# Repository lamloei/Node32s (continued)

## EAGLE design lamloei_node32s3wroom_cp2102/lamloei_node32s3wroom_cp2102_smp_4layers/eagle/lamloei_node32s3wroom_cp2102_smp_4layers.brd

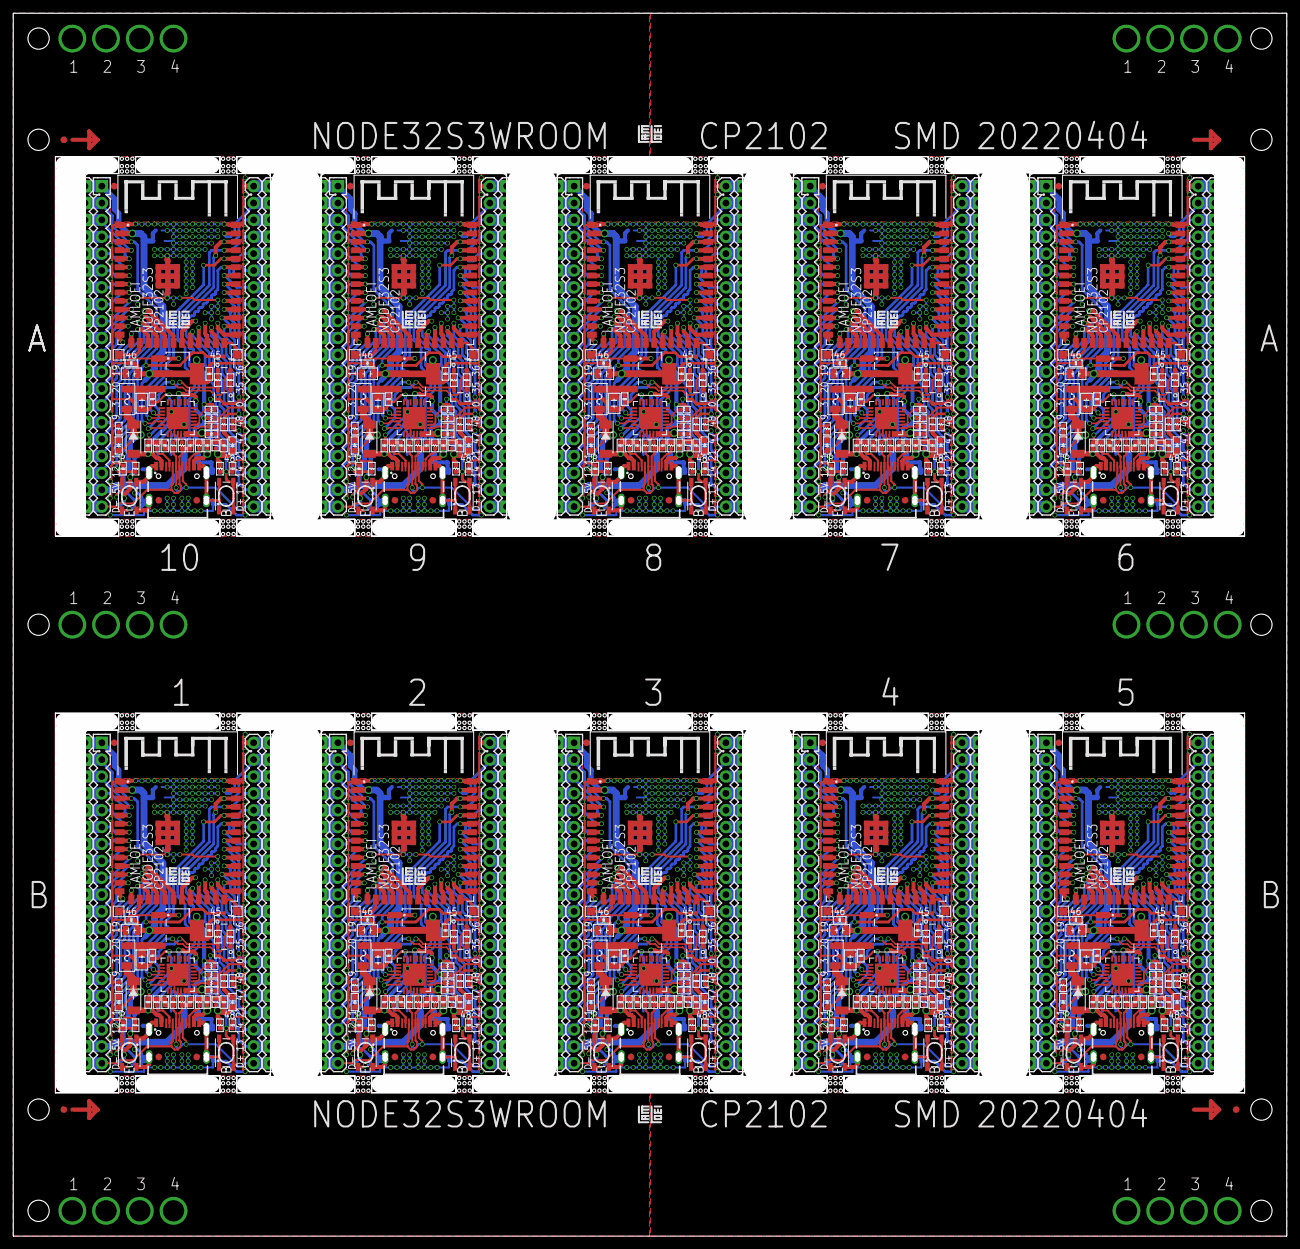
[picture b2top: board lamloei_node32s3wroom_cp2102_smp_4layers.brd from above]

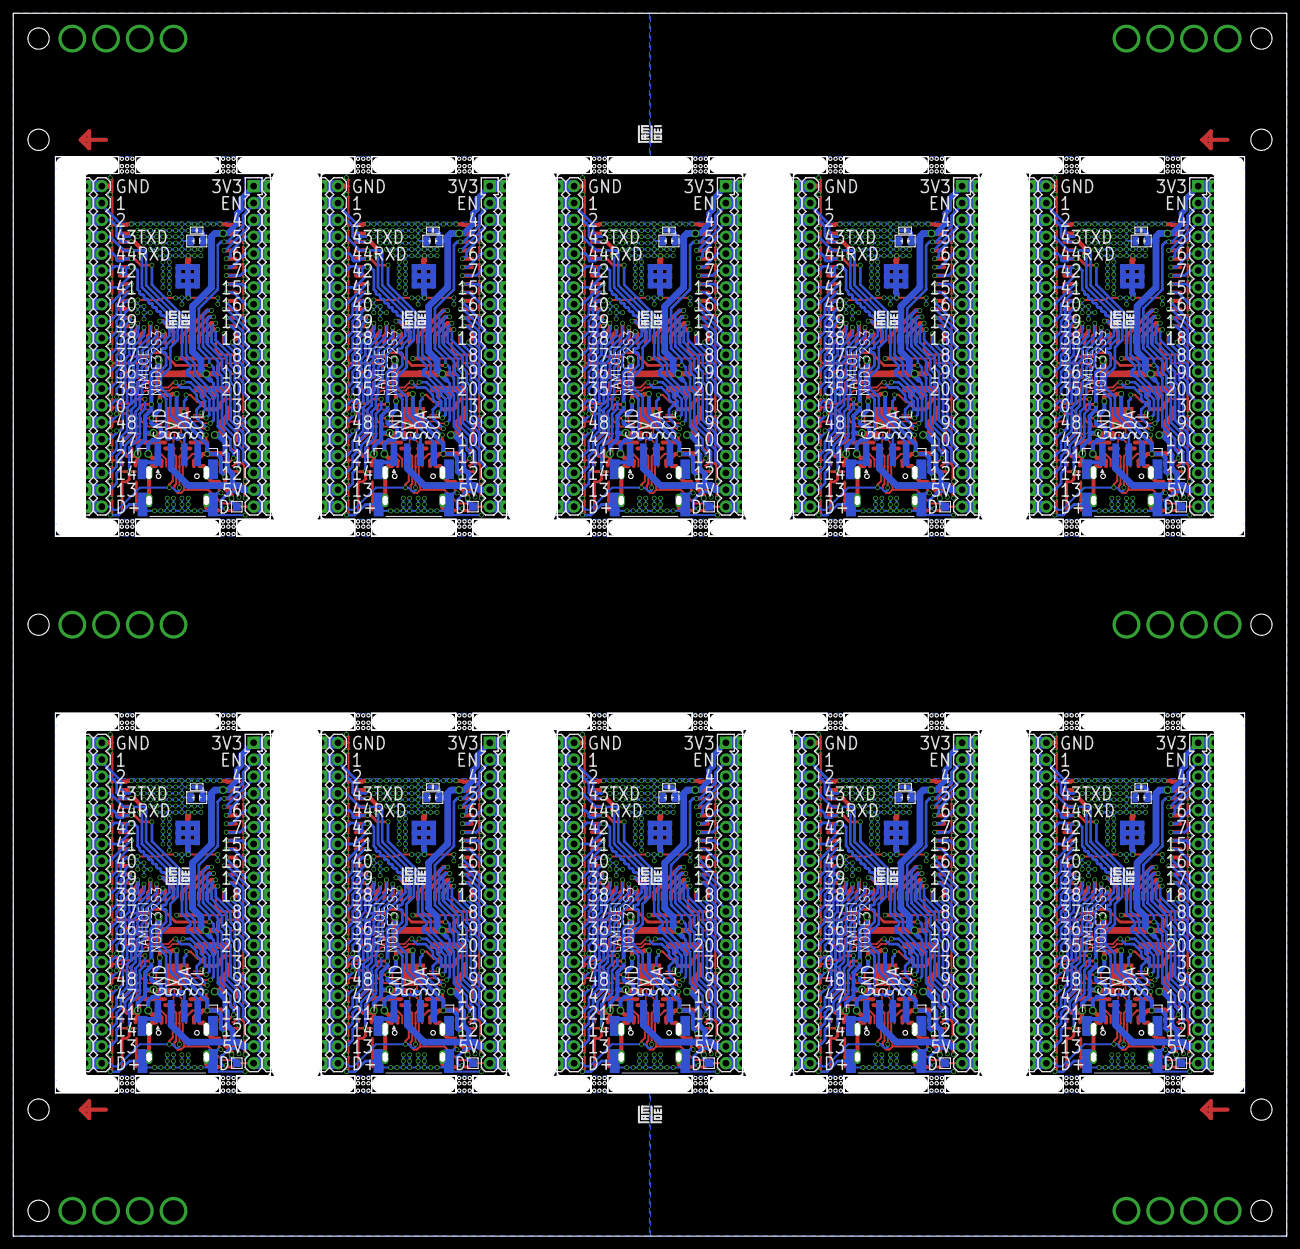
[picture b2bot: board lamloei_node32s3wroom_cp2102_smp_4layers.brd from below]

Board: 4 copper layers, 191.8 x 184.2 mm, 557 parts (52 on the bottom side), 560 nets.

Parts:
C1, C20, C33, C46, C59, C72, C85, C98, C111, C124: 1u; GRM155R70J105KA12D
C2, C3, C6, C7, C8, C10, C11, C13, C16, C17, C18, C19, C22, C24, C25, C26, C29, C30, C31, C32, C35, C37, C38, C39, C42, C43, C44, C45, C48, C50, C51, C52, C55, C56, C57, C58, C61, C63, C64, C65, C68, C69, C70, C71, C74, C76, C77, C78, C81, C82, C83, C84, C87, C89, C90, C91, C94, C95, C96, C97, C100, C102, C103, C104, C107, C108, C109, C110, C113, C115, C116, C117, C120, C121, C122, C123, C126, C128, C129, C130: 100n; GCM155R71H104KE02D
C4, C5, C14, C15, C27, C28, C40, C41, C53, C54, C66, C67, C79, C80, C92, C93, C105, C106, C118, C119: 47p; GCM1555C1H470JA16D
C9, C12, C21, C23, C34, C36, C47, C49, C60, C62, C73, C75, C86, C88, C99, C101, C112, C114, C125, C127: 22u; GCM21BR71H105KA03L
CB1, CB3, CB5, CB7, CB9, CB11, CB13, CB15, CB17, CB19: 22u; GCM21BR71H105KA03L
CB2, CB4, CB6, CB8, CB10, CB12, CB14, CB16, CB18, CB20: 100n; GCM155R71H104KE02D
D1, D2, D3, D4, D5, D6, D7, D8, D9, D10: PMEG4050EP,115
F1, F2, F3, F4, F5, F6, F7, F8, F9, F10: MF-NSMF050-2
J1, J2, J7, J8, J13, J14, J19, J20, J25, J26, J31, J32, J37, J38, J43, J44, J49, J50, J55, J56: 1 20P 2.54MM; HEADER-120
J3, J4, J9, J10, J15, J16, J21, J22, J27, J28, J33, J34, J39, J40, J45, J46, J51, J52, J57, J58: HEADER-101-SMD
J5, J6, J11, J12, J17, J18, J23, J24, J29, J30, J35, J36, J41, J42, J47, J48, J53, J54, J59, J60: HEADER-120
JB1, JB3, JB5, JB7, JB9, JB11, JB13, JB15, JB17, JB19: 1 4P 2.0MM; A2012WR-S-4P
JB2, JB4, JB6, JB8, JB10, JB12, JB14, JB16, JB18, JB20: HEADER-101-SMD
LED1, LED3, LED5, LED7, LED9, LED11, LED13, LED15, LED17, LED19: BLUE; 19-217BHC-ZL1M2RY3T
LED2, LED4, LED6, LED8, LED10, LED12, LED14, LED16, LED18, LED20: YELLOW; 19-213/Y2C-CQ2R2L/3T(CY)
Q1, Q2, Q3, Q4, Q5, Q6, Q7, Q8, Q9, Q10, Q11, Q12, Q13, Q14, Q15, Q16, Q17, Q18, Q19, Q20: BC847B,215
R1, R2, R9, R12, R13, R14, R19, R20, R21, R24, R25, R26, R33, R34, R35, R38, R39, R40, R47, R48, R49, R52, R53, R54, R61, R62, R63, R66, R67, R68, R75, R76, R77, R80, R81, R82, R89, R90, R91, R94, R95, R96, R103, R104, R105, R108, R109, R110, R117, R118, R119, R122, R123, R124, R131, R132, R133, R136, R137, R138: 12K; R0402
R3, R6, R17, R18, R31, R32, R45, R46, R59, R60, R73, R74, R87, R88, R101, R102, R115, R116, R129, R130: 5K1; R0402
R4, R5, R15, R16, R29, R30, R43, R44, R57, R58, R71, R72, R85, R86, R99, R100, R113, R114, R127, R128: 27R; R0402
R7, R8, R22, R23, R36, R37, R50, R51, R64, R65, R78, R79, R92, R93, R106, R107, R120, R121, R134, R135: 2K2; R0402
R10, R28, R42, R56, R70, R84, R98, R112, R126, R140: 47K; R0402
R11, R27, R41, R55, R69, R83, R97, R111, R125, R139: 24K; R0402
SW1, SW2, SW3, SW4, SW5, SW6, SW7, SW8, SW9, SW10, SW11, SW12, SW13, SW14, SW15, SW16, SW17, SW18, SW19, SW20: K2-1808SN-A4SW-01
TZ1, TZ2, TZ3, TZ4, TZ5, TZ6, TZ7, TZ8, TZ9, TZ10: LXES15AAA1-153
U1, U5, U8, U11, U14, U17, U20, U23, U26, U29: ESP32-S3-WROOM
U2, U6, U9, U12, U15, U18, U21, U24, U27, U30: CP2102N-A02-GQFN28R
U3, U4, U7, U10, U13, U16, U19, U22, U25, U28: LM1117MPX-3.3/NOPB
USB1, USB2, USB3, USB4, USB5, USB6, USB7, USB8, USB9, USB10: TYPE-C-31-M-12
ZFC1, ZFC2, ZFC3: FIDUCIAL1X2; FIDUCIAL-1X2
ZFD1, ZFD2, ZFD3, ZFD4, ZFD5, ZFD6, ZFD7, ZFD8, ZFD9, ZFD10, ZFD11, ZFD12, ZFD13, ZFD14, ZFD15, ZFD16, ZFD17, ZFD18, ZFD19, ZFD20, ZFD21, ZFD22, ZFD23, ZFD24, ZFD25, ZFD26, ZFD27, ZFD28, ZFD29, ZFD30: FIDUCIAL1X2; FIDUCIAL-1X2
ZL1, ZL2, ZL3, ZL4, ZL5, ZL6, ZL7, ZL8, ZL9, ZL10, ZL11, ZL12, ZL13, ZL14, ZL15, ZL16, ZL17, ZL18, ZL19, ZL20: LAMLEOI_LOGO_3
ZLC1, ZLC2, ZLC3, ZLC4: LAMLEOI_LOGO_3

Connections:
3.3V: C7.2, C8.2, C11.2, C12.2, C13.2, CB1.2, CB2.2, J1.P1, J5.P1, LED2.2, R1.2, R2.2, R12.1, TZ1.2, U1.2, U2.6, U2.7, U3.2, U3.4
3.3V1: C18.2, C23.2, C24.2, C25.2, C26.2, CB3.2, CB4.2, J7.P1, J11.P1, LED4.2, R19.2, R20.2, R26.1, TZ2.2, U4.2, U4.4, U5.2, U6.6, U6.7
3.3V2: C31.2, C36.2, C37.2, C38.2, C39.2, CB5.2, CB6.2, J13.P1, J17.P1, LED6.2, R33.2, R34.2, R40.1, TZ3.2, U7.2, U7.4, U8.2, U9.6, U9.7
3.3V3: C44.2, C49.2, C50.2, C51.2, C52.2, CB7.2, CB8.2, J19.P1, J23.P1, LED8.2, R47.2, R48.2, R54.1, TZ4.2, U10.2, U10.4, U11.2, U12.6, U12.7
3.3V4: C57.2, C62.2, C63.2, C64.2, C65.2, CB9.2, CB10.2, J25.P1, J29.P1, LED10.2, R61.2, R62.2, R68.1, TZ5.2, U13.2, U13.4, U14.2, U15.6, U15.7
3.3V5: C70.2, C75.2, C76.2, C77.2, C78.2, CB11.2, CB12.2, J31.P1, J35.P1, LED12.2, R75.2, R76.2, R82.1, TZ6.2, U16.2, U16.4, U17.2, U18.6, U18.7
3.3V6: C83.2, C88.2, C89.2, C90.2, C91.2, CB13.2, CB14.2, J37.P1, J41.P1, LED14.2, R89.2, R90.2, R96.1, TZ7.2, U19.2, U19.4, U20.2, U21.6, U21.7
3.3V7: C96.2, C101.2, C102.2, C103.2, C104.2, CB15.2, CB16.2, J43.P1, J47.P1, LED16.2, R103.2, R104.2, R110.1, TZ8.2, U22.2, U22.4, U23.2, U24.6, U24.7
3.3V8: C109.2, C114.2, C115.2, C116.2, C117.2, CB17.2, CB18.2, J49.P1, J53.P1, LED18.2, R117.2, R118.2, R124.1, TZ9.2, U25.2, U25.4, U26.2, U27.6, U27.7
3.3V9: C122.2, C127.2, C128.2, C129.2, C130.2, CB19.2, CB20.2, J55.P1, J59.P1, LED20.2, R131.2, R132.2, R138.1, TZ10.2, U28.2, U28.4, U29.2, U30.6, U30.7
5V: D1.1, F1.1, J1.P19, J5.P19, JB1.2, LED1.2
5V1: D2.1, F2.1, J7.P19, J11.P19, JB3.2, LED3.2
5V2: D3.1, F3.1, J13.P19, J17.P19, JB5.2, LED5.2
5V3: D4.1, F4.1, J19.P19, J23.P19, JB7.2, LED7.2
5V4: D5.1, F5.1, J25.P19, J29.P19, JB9.2, LED9.2
5V5: D6.1, F6.1, J31.P19, J35.P19, JB11.2, LED11.2
5V6: D7.1, F7.1, J37.P19, J41.P19, JB13.2, LED13.2
5V7: D8.1, F8.1, J43.P19, J47.P19, JB15.2, LED15.2
5V8: D9.1, F9.1, J49.P19, J53.P19, JB17.2, LED17.2
5V9: D10.1, F10.1, J55.P19, J59.P19, JB19.2, LED19.2
CC1: R3.2, USB1.A5
CC2: R6.2, USB1.B5
CC3: R17.2, USB2.A5
CC4: R18.2, USB2.B5
CC5: R31.2, USB3.A5
CC6: R32.2, USB3.B5
CC7: R45.2, USB4.A5
CC8: R46.2, USB4.B5
CC9: R59.2, USB5.A5
CC10: R60.2, USB5.B5
CC11: R73.2, USB6.A5
CC12: R74.2, USB6.B5
CC13: R87.2, USB7.A5
CC14: R88.2, USB7.B5
CC15: R101.2, USB8.A5
CC16: R102.2, USB8.B5
CC17: R115.2, USB9.A5
CC18: R116.2, USB9.B5
CC19: R129.2, USB10.A5
CC20: R130.2, USB10.B5
DM: C5.2, J1.P20, J5.P20, R5.1, USB1.A7, USB1.B7
DM1: C14.2, J7.P20, J11.P20, R16.1, USB2.A7, USB2.B7
DM2: C27.2, J13.P20, J17.P20, R30.1, USB3.A7, USB3.B7
DM3: C40.2, J19.P20, J23.P20, R44.1, USB4.A7, USB4.B7
DM4: C53.2, J25.P20, J29.P20, R58.1, USB5.A7, USB5.B7
DM5: C66.2, J31.P20, J35.P20, R72.1, USB6.A7, USB6.B7
DM6: C79.2, J37.P20, J41.P20, R86.1, USB7.A7, USB7.B7
DM7: C92.2, J43.P20, J47.P20, R100.1, USB8.A7, USB8.B7
DM8: C105.2, J49.P20, J53.P20, R114.1, USB9.A7, USB9.B7
DM9: C118.2, J55.P20, J59.P20, R128.1, USB10.A7, USB10.B7
DP: C4.2, J2.P20, J6.P20, R4.1, USB1.A6, USB1.B6
DP1: C15.2, J8.P20, J12.P20, R15.1, USB2.A6, USB2.B6
DP2: C28.2, J14.P20, J18.P20, R29.1, USB3.A6, USB3.B6
DP3: C41.2, J20.P20, J24.P20, R43.1, USB4.A6, USB4.B6
DP4: C54.2, J26.P20, J30.P20, R57.1, USB5.A6, USB5.B6
DP5: C67.2, J32.P20, J36.P20, R71.1, USB6.A6, USB6.B6
DP6: C80.2, J38.P20, J42.P20, R85.1, USB7.A6, USB7.B6
DP7: C93.2, J44.P20, J48.P20, R99.1, USB8.A6, USB8.B6
DP8: C106.2, J50.P20, J54.P20, R113.1, USB9.A6, USB9.B6
DP9: C119.2, J56.P20, J60.P20, R127.1, USB10.A6, USB10.B6
DTR: Q1.E, R13.1, U2.28
DTR1: Q4.E, R24.1, U6.28
DTR2: Q6.E, R38.1, U9.28
DTR3: Q8.E, R52.1, U12.28
DTR4: Q10.E, R66.1, U15.28
DTR5: Q12.E, R80.1, U18.28
DTR6: Q14.E, R94.1, U21.28
DTR7: Q16.E, R108.1, U24.28
DTR8: Q18.E, R122.1, U27.28
DTR9: Q20.E, R136.1, U30.28
EN: C1.2, J1.P2, J5.P2, Q2.C, R1.1, SW1.3, SW1.4, U1.3
EN1: C20.2, J7.P2, J11.P2, Q3.C, R19.1, SW3.3, SW3.4, U5.3
EN2: C33.2, J13.P2, J17.P2, Q5.C, R33.1, SW5.3, SW5.4, U8.3
EN3: C46.2, J19.P2, J23.P2, Q7.C, R47.1, SW7.3, SW7.4, U11.3
EN4: C59.2, J25.P2, J29.P2, Q9.C, R61.1, SW9.3, SW9.4, U14.3
EN5: C72.2, J31.P2, J35.P2, Q11.C, R75.1, SW11.3, SW11.4, U17.3
EN6: C85.2, J37.P2, J41.P2, Q13.C, R89.1, SW13.3, SW13.4, U20.3
EN7: C98.2, J43.P2, J47.P2, Q15.C, R103.1, SW15.3, SW15.4, U23.3
EN8: C111.2, J49.P2, J53.P2, Q17.C, R117.1, SW17.3, SW17.4, U26.3
EN9: C124.2, J55.P2, J59.P2, Q19.C, R131.1, SW19.3, SW19.4, U29.3
GND: C1.1, C2.1, C3.1, C4.1, C5.1, C6.1, C7.1, C8.1, C9.1, C10.1, C11.1, C12.1, C13.1, CB1.1, CB2.1, J2.P1, J6.P1, JB1.1, JB1.G1, JB1.G2, JB1.G3, JB1.G4, R3.1, R6.1, R7.1, R9.1, R10.1, SW1.1, SW1.2, SW2.1, SW2.2, TZ1.1, U1.1, U1.1.1, U1.1.2, U1.1.3, U1.1.4, U1.1.5, U1.1.6, U1.1.7, U1.1.8, U1.1.9, U1.1.10, U1.1.11, U1.1.12, U1.1.13, U1.1.14, U1.1.15, U1.1.16, U1.1.17, U1.1.18, U1.40, U2.3, U2.29, U3.1, USB1.A1B12, USB1.B1A12, USB1.S1, USB1.S2, USB1.S3, USB1.S4
GND1: C14.1, C15.1, C16.1, C17.1, C18.1, C19.1, C20.1, C21.1, C22.1, C23.1, C24.1, C25.1, C26.1, CB3.1, CB4.1, J8.P1, J12.P1, JB3.1, JB3.G1, JB3.G2, JB3.G3, JB3.G4, R17.1, R18.1, R21.1, R22.1, R28.1, SW3.1, SW3.2, SW4.1, SW4.2, TZ2.1, U4.1, U5.1, U5.1.1, U5.1.2, U5.1.3, U5.1.4, U5.1.5, U5.1.6, U5.1.7, U5.1.8, U5.1.9, U5.1.10, U5.1.11, U5.1.12, U5.1.13, U5.1.14, U5.1.15, U5.1.16, U5.1.17, U5.1.18, U5.40, U6.3, U6.29, USB2.A1B12, USB2.B1A12, USB2.S1, USB2.S2, USB2.S3, USB2.S4
GND2: C27.1, C28.1, C29.1, C30.1, C31.1, C32.1, C33.1, C34.1, C35.1, C36.1, C37.1, C38.1, C39.1, CB5.1, CB6.1, J14.P1, J18.P1, JB5.1, JB5.G1, JB5.G2, JB5.G3, JB5.G4, R31.1, R32.1, R35.1, R36.1, R42.1, SW5.1, SW5.2, SW6.1, SW6.2, TZ3.1, U7.1, U8.1, U8.1.1, U8.1.2, U8.1.3, U8.1.4, U8.1.5, U8.1.6, U8.1.7, U8.1.8, U8.1.9, U8.1.10, U8.1.11, U8.1.12, U8.1.13, U8.1.14, U8.1.15, U8.1.16, U8.1.17, U8.1.18, U8.40, U9.3, U9.29, USB3.A1B12, USB3.B1A12, USB3.S1, USB3.S2, USB3.S3, USB3.S4
GND3: C40.1, C41.1, C42.1, C43.1, C44.1, C45.1, C46.1, C47.1, C48.1, C49.1, C50.1, C51.1, C52.1, CB7.1, CB8.1, J20.P1, J24.P1, JB7.1, JB7.G1, JB7.G2, JB7.G3, JB7.G4, R45.1, R46.1, R49.1, R50.1, R56.1, SW7.1, SW7.2, SW8.1, SW8.2, TZ4.1, U10.1, U11.1, U11.1.1, U11.1.2, U11.1.3, U11.1.4, U11.1.5, U11.1.6, U11.1.7, U11.1.8, U11.1.9, U11.1.10, U11.1.11, U11.1.12, U11.1.13, U11.1.14, U11.1.15, U11.1.16, U11.1.17, U11.1.18, U11.40, U12.3, U12.29, USB4.A1B12, USB4.B1A12, USB4.S1, USB4.S2, USB4.S3, USB4.S4
GND4: C53.1, C54.1, C55.1, C56.1, C57.1, C58.1, C59.1, C60.1, C61.1, C62.1, C63.1, C64.1, C65.1, CB9.1, CB10.1, J26.P1, J30.P1, JB9.1, JB9.G1, JB9.G2, JB9.G3, JB9.G4, R59.1, R60.1, R63.1, R64.1, R70.1, SW9.1, SW9.2, SW10.1, SW10.2, TZ5.1, U13.1, U14.1, U14.1.1, U14.1.2, U14.1.3, U14.1.4, U14.1.5, U14.1.6, U14.1.7, U14.1.8, U14.1.9, U14.1.10, U14.1.11, U14.1.12, U14.1.13, U14.1.14, U14.1.15, U14.1.16, U14.1.17, U14.1.18, U14.40, U15.3, U15.29, USB5.A1B12, USB5.B1A12, USB5.S1, USB5.S2, USB5.S3, USB5.S4
GND5: C66.1, C67.1, C68.1, C69.1, C70.1, C71.1, C72.1, C73.1, C74.1, C75.1, C76.1, C77.1, C78.1, CB11.1, CB12.1, J32.P1, J36.P1, JB11.1, JB11.G1, JB11.G2, JB11.G3, JB11.G4, R73.1, R74.1, R77.1, R78.1, R84.1, SW11.1, SW11.2, SW12.1, SW12.2, TZ6.1, U16.1, U17.1, U17.1.1, U17.1.2, U17.1.3, U17.1.4, U17.1.5, U17.1.6, U17.1.7, U17.1.8, U17.1.9, U17.1.10, U17.1.11, U17.1.12, U17.1.13, U17.1.14, U17.1.15, U17.1.16, U17.1.17, U17.1.18, U17.40, U18.3, U18.29, USB6.A1B12, USB6.B1A12, USB6.S1, USB6.S2, USB6.S3, USB6.S4
GND6: C79.1, C80.1, C81.1, C82.1, C83.1, C84.1, C85.1, C86.1, C87.1, C88.1, C89.1, C90.1, C91.1, CB13.1, CB14.1, J38.P1, J42.P1, JB13.1, JB13.G1, JB13.G2, JB13.G3, JB13.G4, R87.1, R88.1, R91.1, R92.1, R98.1, SW13.1, SW13.2, SW14.1, SW14.2, TZ7.1, U19.1, U20.1, U20.1.1, U20.1.2, U20.1.3, U20.1.4, U20.1.5, U20.1.6, U20.1.7, U20.1.8, U20.1.9, U20.1.10, U20.1.11, U20.1.12, U20.1.13, U20.1.14, U20.1.15, U20.1.16, U20.1.17, U20.1.18, U20.40, U21.3, U21.29, USB7.A1B12, USB7.B1A12, USB7.S1, USB7.S2, USB7.S3, USB7.S4
GND7: C92.1, C93.1, C94.1, C95.1, C96.1, C97.1, C98.1, C99.1, C100.1, C101.1, C102.1, C103.1, C104.1, CB15.1, CB16.1, J44.P1, J48.P1, JB15.1, JB15.G1, JB15.G2, JB15.G3, JB15.G4, R101.1, R102.1, R105.1, R106.1, R112.1, SW15.1, SW15.2, SW16.1, SW16.2, TZ8.1, U22.1, U23.1, U23.1.1, U23.1.2, U23.1.3, U23.1.4, U23.1.5, U23.1.6, U23.1.7, U23.1.8, U23.1.9, U23.1.10, U23.1.11, U23.1.12, U23.1.13, U23.1.14, U23.1.15, U23.1.16, U23.1.17, U23.1.18, U23.40, U24.3, U24.29, USB8.A1B12, USB8.B1A12, USB8.S1, USB8.S2, USB8.S3, USB8.S4
GND8: C105.1, C106.1, C107.1, C108.1, C109.1, C110.1, C111.1, C112.1, C113.1, C114.1, C115.1, C116.1, C117.1, CB17.1, CB18.1, J50.P1, J54.P1, JB17.1, JB17.G1, JB17.G2, JB17.G3, JB17.G4, R115.1, R116.1, R119.1, R120.1, R126.1, SW17.1, SW17.2, SW18.1, SW18.2, TZ9.1, U25.1, U26.1, U26.1.1, U26.1.2, U26.1.3, U26.1.4, U26.1.5, U26.1.6, U26.1.7, U26.1.8, U26.1.9, U26.1.10, U26.1.11, U26.1.12, U26.1.13, U26.1.14, U26.1.15, U26.1.16, U26.1.17, U26.1.18, U26.40, U27.3, U27.29, USB9.A1B12, USB9.B1A12, USB9.S1, USB9.S2, USB9.S3, USB9.S4
GND9: C118.1, C119.1, C120.1, C121.1, C122.1, C123.1, C124.1, C125.1, C126.1, C127.1, C128.1, C129.1, C130.1, CB19.1, CB20.1, J56.P1, J60.P1, JB19.1, JB19.G1, JB19.G2, JB19.G3, JB19.G4, R129.1, R130.1, R133.1, R134.1, R140.1, SW19.1, SW19.2, SW20.1, SW20.2, TZ10.1, U28.1, U29.1, U29.1.1, U29.1.2, U29.1.3, U29.1.4, U29.1.5, U29.1.6, U29.1.7, U29.1.8, U29.1.9, U29.1.10, U29.1.11, U29.1.12, U29.1.13, U29.1.14, U29.1.15, U29.1.16, U29.1.17, U29.1.18, U29.40, U30.3, U30.29, USB10.A1B12, USB10.B1A12, USB10.S1, USB10.S2, USB10.S3, USB10.S4
IO0: C2.2, J2.P14, J6.P14, Q1.C, R2.1, SW2.3, SW2.4, U1.27
IO1: J2.P2, J6.P2, U1.39
IO2: J2.P3, J6.P3, JB1.4, U1.38
IO3: J1.P14, J5.P14, U1.15
IO4: J1.P3, J5.P3, U1.4
IO5: J1.P4, J5.P4, U1.5
IO6: J1.P5, J5.P5, U1.6
IO7: J1.P6, J5.P6, U1.7
IO8: J1.P11, J5.P11, U1.12
IO9: J1.P15, J5.P15, U1.17
IO10: J1.P16, J5.P16, U1.18
IO11: J1.P17, J5.P17, U1.19
IO12: J1.P18, J5.P18, U1.20
IO13: J2.P19, J6.P19, U1.21
IO14: J2.P18, J6.P18, U1.22
IO15: J1.P7, J5.P7, U1.8
IO16: J1.P8, J5.P8, U1.9
IO17: J1.P9, J5.P9, U1.10
IO18: J1.P10, J5.P10, U1.11
IO19: J1.P12, J5.P12, U1.13
IO20: J1.P13, J5.P13, U1.14
IO21: J2.P17, J6.P17, U1.23
IO22: J7.P17, J11.P17, U5.19
IO23: J7.P5, J11.P5, U5.6
IO24: J7.P6, J11.P6, U5.7
IO25: J7.P11, J11.P11, U5.12
IO26: J7.P15, J11.P15, U5.17
IO27: J7.P16, J11.P16, U5.18
IO28: C19.2, J8.P14, J12.P14, Q4.C, R20.1, SW4.3, SW4.4, U5.27
IO29: J7.P3, J11.P3, U5.4
IO30: J7.P4, J11.P4, U5.5
IO31: J7.P7, J11.P7, U5.8
IO32: J7.P8, J11.P8, U5.9
IO33: J7.P9, J11.P9, U5.10
IO34: J7.P10, J11.P10, U5.11
IO35: J2.P13, J6.P13, U1.28
IO36: J2.P12, J6.P12, U1.29
IO37: J2.P11, J6.P11, U1.30
IO38: J2.P10, J6.P10, U1.31
IO39: J2.P9, J6.P9, U1.32
IO40: J2.P8, J6.P8, U1.33
IO41: J2.P7, J6.P7, U1.34
IO42: J2.P6, J6.P6, JB1.3, U1.35
IO43: J7.P12, J11.P12, U5.13
IO44: J8.P17, J12.P17, U5.23
IO45: J4.P$1, U1.26
IO46: J3.P$1, U1.16
IO47: J2.P16, J6.P16, R9.2, U1.24
IO48: J2.P15, J6.P15, R8.1, U1.25
IO49: J7.P13, J11.P13, U5.14
IO50: J7.P14, J11.P14, U5.15
IO51: J7.P18, J11.P18, U5.20
IO52: J8.P19, J12.P19, U5.21
IO53: J8.P18, J12.P18, U5.22
IO54: J8.P16, J12.P16, R21.2, U5.24
IO55: J8.P15, J12.P15, R23.1, U5.25
IO56: J8.P6, J12.P6, JB3.3, U5.35
IO57: J8.P13, J12.P13, U5.28
IO58: J8.P12, J12.P12, U5.29
IO59: J8.P11, J12.P11, U5.30
IO60: J8.P10, J12.P10, U5.31
IO61: J8.P9, J12.P9, U5.32
IO62: J8.P8, J12.P8, U5.33
IO63: J8.P7, J12.P7, U5.34
IO64: J8.P3, J12.P3, JB3.4, U5.38
IO65: J8.P2, J12.P2, U5.39
IO66: J10.P$1, U5.26
IO67: J9.P$1, U5.16
IO68: J13.P17, J17.P17, U8.19
IO69: J13.P5, J17.P5, U8.6
IO70: J13.P6, J17.P6, U8.7
IO71: J13.P11, J17.P11, U8.12
IO72: J13.P15, J17.P15, U8.17
IO73: J13.P16, J17.P16, U8.18
IO74: C32.2, J14.P14, J18.P14, Q6.C, R34.1, SW6.3, SW6.4, U8.27
IO75: J13.P3, J17.P3, U8.4
IO76: J13.P4, J17.P4, U8.5
IO77: J13.P7, J17.P7, U8.8
IO78: J13.P8, J17.P8, U8.9
IO79: J13.P9, J17.P9, U8.10
IO80: J13.P10, J17.P10, U8.11
IO81: J13.P12, J17.P12, U8.13
IO82: J14.P17, J18.P17, U8.23
IO83: J13.P13, J17.P13, U8.14
IO84: J13.P14, J17.P14, U8.15
IO85: J13.P18, J17.P18, U8.20
IO86: J14.P19, J18.P19, U8.21
IO87: J14.P18, J18.P18, U8.22
IO88: J14.P16, J18.P16, R35.2, U8.24
IO89: J14.P15, J18.P15, R37.1, U8.25
IO90: J14.P6, J18.P6, JB5.3, U8.35
IO91: J14.P13, J18.P13, U8.28
IO92: J14.P12, J18.P12, U8.29
IO93: J14.P11, J18.P11, U8.30
IO94: J14.P10, J18.P10, U8.31
IO95: J14.P9, J18.P9, U8.32
IO96: J14.P8, J18.P8, U8.33
IO97: J14.P7, J18.P7, U8.34
IO98: J14.P3, J18.P3, JB5.4, U8.38
IO99: J14.P2, J18.P2, U8.39
IO100: J16.P$1, U8.26
IO101: J15.P$1, U8.16
IO102: J19.P17, J23.P17, U11.19
IO103: J19.P5, J23.P5, U11.6
IO104: J19.P6, J23.P6, U11.7
IO105: J19.P11, J23.P11, U11.12
IO106: J19.P15, J23.P15, U11.17
IO107: J19.P16, J23.P16, U11.18
IO108: C45.2, J20.P14, J24.P14, Q8.C, R48.1, SW8.3, SW8.4, U11.27
IO109: J19.P3, J23.P3, U11.4
IO110: J19.P4, J23.P4, U11.5
IO111: J19.P7, J23.P7, U11.8
IO112: J19.P8, J23.P8, U11.9
IO113: J19.P9, J23.P9, U11.10
IO114: J19.P10, J23.P10, U11.11
IO115: J19.P12, J23.P12, U11.13
IO116: J20.P17, J24.P17, U11.23
IO117: J19.P13, J23.P13, U11.14
IO118: J19.P14, J23.P14, U11.15
IO119: J19.P18, J23.P18, U11.20
IO120: J20.P19, J24.P19, U11.21
IO121: J20.P18, J24.P18, U11.22
IO122: J20.P16, J24.P16, R49.2, U11.24
IO123: J20.P15, J24.P15, R51.1, U11.25
IO124: J20.P6, J24.P6, JB7.3, U11.35
IO125: J20.P13, J24.P13, U11.28
IO126: J20.P12, J24.P12, U11.29
IO127: J20.P11, J24.P11, U11.30
IO128: J20.P10, J24.P10, U11.31
IO129: J20.P9, J24.P9, U11.32
IO130: J20.P8, J24.P8, U11.33
IO131: J20.P7, J24.P7, U11.34
IO132: J20.P3, J24.P3, JB7.4, U11.38
IO133: J20.P2, J24.P2, U11.39
IO134: J22.P$1, U11.26
IO135: J21.P$1, U11.16
IO136: J25.P17, J29.P17, U14.19
IO137: J25.P5, J29.P5, U14.6
IO138: J25.P6, J29.P6, U14.7
IO139: J25.P11, J29.P11, U14.12
IO140: J25.P15, J29.P15, U14.17
IO141: J25.P16, J29.P16, U14.18
IO142: C58.2, J26.P14, J30.P14, Q10.C, R62.1, SW10.3, SW10.4, U14.27
IO143: J25.P3, J29.P3, U14.4
IO144: J25.P4, J29.P4, U14.5
IO145: J25.P7, J29.P7, U14.8
IO146: J25.P8, J29.P8, U14.9
IO147: J25.P9, J29.P9, U14.10
IO148: J25.P10, J29.P10, U14.11
IO149: J25.P12, J29.P12, U14.13
IO150: J26.P17, J30.P17, U14.23
IO151: J25.P13, J29.P13, U14.14
IO152: J25.P14, J29.P14, U14.15
IO153: J25.P18, J29.P18, U14.20
IO154: J26.P19, J30.P19, U14.21
IO155: J26.P18, J30.P18, U14.22
IO156: J26.P16, J30.P16, R63.2, U14.24
IO157: J26.P15, J30.P15, R65.1, U14.25
IO158: J26.P6, J30.P6, JB9.3, U14.35
IO159: J26.P13, J30.P13, U14.28
IO160: J26.P12, J30.P12, U14.29
IO161: J26.P11, J30.P11, U14.30
IO162: J26.P10, J30.P10, U14.31
IO163: J26.P9, J30.P9, U14.32
IO164: J26.P8, J30.P8, U14.33
IO165: J26.P7, J30.P7, U14.34
IO166: J26.P3, J30.P3, JB9.4, U14.38
IO167: J26.P2, J30.P2, U14.39
IO168: J28.P$1, U14.26
IO169: J27.P$1, U14.16
IO170: J31.P17, J35.P17, U17.19
IO171: J31.P5, J35.P5, U17.6
IO172: J31.P6, J35.P6, U17.7
IO173: J31.P11, J35.P11, U17.12
IO174: J31.P15, J35.P15, U17.17
IO175: J31.P16, J35.P16, U17.18
IO176: C71.2, J32.P14, J36.P14, Q12.C, R76.1, SW12.3, SW12.4, U17.27
IO177: J31.P3, J35.P3, U17.4
IO178: J31.P4, J35.P4, U17.5
IO179: J31.P7, J35.P7, U17.8
IO180: J31.P8, J35.P8, U17.9
IO181: J31.P9, J35.P9, U17.10
IO182: J31.P10, J35.P10, U17.11
IO183: J31.P12, J35.P12, U17.13
IO184: J32.P17, J36.P17, U17.23
IO185: J31.P13, J35.P13, U17.14
IO186: J31.P14, J35.P14, U17.15
IO187: J31.P18, J35.P18, U17.20
IO188: J32.P19, J36.P19, U17.21
IO189: J32.P18, J36.P18, U17.22
IO190: J32.P16, J36.P16, R77.2, U17.24
IO191: J32.P15, J36.P15, R79.1, U17.25
IO192: J32.P6, J36.P6, JB11.3, U17.35
IO193: J32.P13, J36.P13, U17.28
IO194: J32.P12, J36.P12, U17.29
IO195: J32.P11, J36.P11, U17.30
IO196: J32.P10, J36.P10, U17.31
IO197: J32.P9, J36.P9, U17.32
IO198: J32.P8, J36.P8, U17.33
IO199: J32.P7, J36.P7, U17.34
IO200: J32.P3, J36.P3, JB11.4, U17.38
IO201: J32.P2, J36.P2, U17.39
IO202: J34.P$1, U17.26
IO203: J33.P$1, U17.16
IO204: J37.P17, J41.P17, U20.19
IO205: J37.P5, J41.P5, U20.6
IO206: J37.P6, J41.P6, U20.7
IO207: J37.P11, J41.P11, U20.12
IO208: J37.P15, J41.P15, U20.17
IO209: J37.P16, J41.P16, U20.18
IO210: C84.2, J38.P14, J42.P14, Q14.C, R90.1, SW14.3, SW14.4, U20.27
IO211: J37.P3, J41.P3, U20.4
IO212: J37.P4, J41.P4, U20.5
IO213: J37.P7, J41.P7, U20.8
IO214: J37.P8, J41.P8, U20.9
IO215: J37.P9, J41.P9, U20.10
IO216: J37.P10, J41.P10, U20.11
IO217: J37.P12, J41.P12, U20.13
IO218: J38.P17, J42.P17, U20.23
IO219: J37.P13, J41.P13, U20.14
IO220: J37.P14, J41.P14, U20.15
IO221: J37.P18, J41.P18, U20.20
IO222: J38.P19, J42.P19, U20.21
IO223: J38.P18, J42.P18, U20.22
IO224: J38.P16, J42.P16, R91.2, U20.24
IO225: J38.P15, J42.P15, R93.1, U20.25
IO226: J38.P6, J42.P6, JB13.3, U20.35
IO227: J38.P13, J42.P13, U20.28
IO228: J38.P12, J42.P12, U20.29
IO229: J38.P11, J42.P11, U20.30
IO230: J38.P10, J42.P10, U20.31
IO231: J38.P9, J42.P9, U20.32
IO232: J38.P8, J42.P8, U20.33
IO233: J38.P7, J42.P7, U20.34
IO234: J38.P3, J42.P3, JB13.4, U20.38
IO235: J38.P2, J42.P2, U20.39
IO236: J40.P$1, U20.26
IO237: J39.P$1, U20.16
IO238: J43.P17, J47.P17, U23.19
IO239: J43.P5, J47.P5, U23.6
IO240: J43.P6, J47.P6, U23.7
IO241: J43.P11, J47.P11, U23.12
IO242: J43.P15, J47.P15, U23.17
IO243: J43.P16, J47.P16, U23.18
IO244: C97.2, J44.P14, J48.P14, Q16.C, R104.1, SW16.3, SW16.4, U23.27
IO245: J43.P3, J47.P3, U23.4
IO246: J43.P4, J47.P4, U23.5
IO247: J43.P7, J47.P7, U23.8
IO248: J43.P8, J47.P8, U23.9
IO249: J43.P9, J47.P9, U23.10
IO250: J43.P10, J47.P10, U23.11
IO251: J43.P12, J47.P12, U23.13
IO252: J44.P17, J48.P17, U23.23
IO253: J43.P13, J47.P13, U23.14
IO254: J43.P14, J47.P14, U23.15
IO255: J43.P18, J47.P18, U23.20
IO256: J44.P19, J48.P19, U23.21
IO257: J44.P18, J48.P18, U23.22
IO258: J44.P16, J48.P16, R105.2, U23.24
IO259: J44.P15, J48.P15, R107.1, U23.25
IO260: J44.P6, J48.P6, JB15.3, U23.35
IO261: J44.P13, J48.P13, U23.28
IO262: J44.P12, J48.P12, U23.29
IO263: J44.P11, J48.P11, U23.30
IO264: J44.P10, J48.P10, U23.31
IO265: J44.P9, J48.P9, U23.32
IO266: J44.P8, J48.P8, U23.33
IO267: J44.P7, J48.P7, U23.34
IO268: J44.P3, J48.P3, JB15.4, U23.38
IO269: J44.P2, J48.P2, U23.39
IO270: J46.P$1, U23.26
IO271: J45.P$1, U23.16
IO272: J49.P17, J53.P17, U26.19
IO273: J49.P5, J53.P5, U26.6
IO274: J49.P6, J53.P6, U26.7
IO275: J49.P11, J53.P11, U26.12
IO276: J49.P15, J53.P15, U26.17
IO277: J49.P16, J53.P16, U26.18
IO278: C110.2, J50.P14, J54.P14, Q18.C, R118.1, SW18.3, SW18.4, U26.27
IO279: J49.P3, J53.P3, U26.4
IO280: J49.P4, J53.P4, U26.5
IO281: J49.P7, J53.P7, U26.8
IO282: J49.P8, J53.P8, U26.9
IO283: J49.P9, J53.P9, U26.10
IO284: J49.P10, J53.P10, U26.11
IO285: J49.P12, J53.P12, U26.13
IO286: J50.P17, J54.P17, U26.23
IO287: J49.P13, J53.P13, U26.14
IO288: J49.P14, J53.P14, U26.15
IO289: J49.P18, J53.P18, U26.20
IO290: J50.P19, J54.P19, U26.21
IO291: J50.P18, J54.P18, U26.22
IO292: J50.P16, J54.P16, R119.2, U26.24
IO293: J50.P15, J54.P15, R121.1, U26.25
IO294: J50.P6, J54.P6, JB17.3, U26.35
IO295: J50.P13, J54.P13, U26.28
IO296: J50.P12, J54.P12, U26.29
IO297: J50.P11, J54.P11, U26.30
IO298: J50.P10, J54.P10, U26.31
IO299: J50.P9, J54.P9, U26.32
IO300: J50.P8, J54.P8, U26.33
IO301: J50.P7, J54.P7, U26.34
IO302: J50.P3, J54.P3, JB17.4, U26.38
IO303: J50.P2, J54.P2, U26.39
IO304: J52.P$1, U26.26
IO305: J51.P$1, U26.16
IO306: J55.P17, J59.P17, U29.19
IO307: J55.P5, J59.P5, U29.6
IO308: J55.P6, J59.P6, U29.7
IO309: J55.P11, J59.P11, U29.12
IO310: J55.P15, J59.P15, U29.17
IO311: J55.P16, J59.P16, U29.18
IO312: C123.2, J56.P14, J60.P14, Q20.C, R132.1, SW20.3, SW20.4, U29.27
IO313: J55.P3, J59.P3, U29.4
IO314: J55.P4, J59.P4, U29.5
IO315: J55.P7, J59.P7, U29.8
IO316: J55.P8, J59.P8, U29.9
IO317: J55.P9, J59.P9, U29.10
IO318: J55.P10, J59.P10, U29.11
IO319: J55.P12, J59.P12, U29.13
IO320: J56.P17, J60.P17, U29.23
IO321: J55.P13, J59.P13, U29.14
IO322: J55.P14, J59.P14, U29.15
IO323: J55.P18, J59.P18, U29.20
IO324: J56.P19, J60.P19, U29.21
IO325: J56.P18, J60.P18, U29.22
IO326: J56.P16, J60.P16, R133.2, U29.24
IO327: J56.P15, J60.P15, R135.1, U29.25
IO328: J56.P6, J60.P6, JB19.3, U29.35
IO329: J56.P13, J60.P13, U29.28
IO330: J56.P12, J60.P12, U29.29
IO331: J56.P11, J60.P11, U29.30
IO332: J56.P10, J60.P10, U29.31
IO333: J56.P9, J60.P9, U29.32
IO334: J56.P8, J60.P8, U29.33
IO335: J56.P7, J60.P7, U29.34
IO336: J56.P3, J60.P3, JB19.4, U29.38
IO337: J56.P2, J60.P2, U29.39
IO338: J58.P$1, U29.26
IO339: J57.P$1, U29.16
unnamed: C9.2, C10.2, F1.2, U3.3
unnamed: LED1.1, R7.2
unnamed: LED2.1, R8.2
unnamed: Q2.B, R13.2
unnamed: Q1.B, R14.2
unnamed: R5.2, U2.5
unnamed: R4.2, U2.4
unnamed: R12.2, U2.9
unnamed: R10.2, R11.2, U2.8
unnamed: C21.2, C22.2, F2.2, U4.3
unnamed: LED3.1, R22.2
unnamed: LED4.1, R23.2
unnamed: Q3.B, R24.2
unnamed: Q4.B, R25.2
unnamed: R16.2, U6.5
unnamed: R15.2, U6.4
unnamed: R26.2, U6.9
unnamed: R27.2, R28.2, U6.8
unnamed: C34.2, C35.2, F3.2, U7.3
unnamed: LED5.1, R36.2
unnamed: LED6.1, R37.2
unnamed: Q5.B, R38.2
unnamed: Q6.B, R39.2
unnamed: R30.2, U9.5
unnamed: R29.2, U9.4
unnamed: R40.2, U9.9
unnamed: R41.2, R42.2, U9.8
unnamed: C47.2, C48.2, F4.2, U10.3
unnamed: LED7.1, R50.2
unnamed: LED8.1, R51.2
unnamed: Q7.B, R52.2
unnamed: Q8.B, R53.2
unnamed: R44.2, U12.5
unnamed: R43.2, U12.4
unnamed: R54.2, U12.9
unnamed: R55.2, R56.2, U12.8
unnamed: C60.2, C61.2, F5.2, U13.3
unnamed: LED9.1, R64.2
unnamed: LED10.1, R65.2
unnamed: Q9.B, R66.2
unnamed: Q10.B, R67.2
unnamed: R58.2, U15.5
unnamed: R57.2, U15.4
unnamed: R68.2, U15.9
unnamed: R69.2, R70.2, U15.8
unnamed: C73.2, C74.2, F6.2, U16.3
unnamed: LED11.1, R78.2
unnamed: LED12.1, R79.2
unnamed: Q11.B, R80.2
unnamed: Q12.B, R81.2
unnamed: R72.2, U18.5
unnamed: R71.2, U18.4
unnamed: R82.2, U18.9
unnamed: R83.2, R84.2, U18.8
unnamed: C86.2, C87.2, F7.2, U19.3
unnamed: LED13.1, R92.2
unnamed: LED14.1, R93.2
unnamed: Q13.B, R94.2
unnamed: Q14.B, R95.2
unnamed: R86.2, U21.5
unnamed: R85.2, U21.4
unnamed: R96.2, U21.9
unnamed: R97.2, R98.2, U21.8
unnamed: C99.2, C100.2, F8.2, U22.3
unnamed: LED15.1, R106.2
unnamed: LED16.1, R107.2
unnamed: Q15.B, R108.2
unnamed: Q16.B, R109.2
unnamed: R100.2, U24.5
unnamed: R99.2, U24.4
unnamed: R110.2, U24.9
unnamed: R111.2, R112.2, U24.8
unnamed: C112.2, C113.2, F9.2, U25.3
unnamed: LED17.1, R120.2
unnamed: LED18.1, R121.2
unnamed: Q17.B, R122.2
unnamed: Q18.B, R123.2
unnamed: R114.2, U27.5
unnamed: R113.2, U27.4
unnamed: R124.2, U27.9
unnamed: R125.2, R126.2, U27.8
unnamed: C125.2, C126.2, F10.2, U28.3
unnamed: LED19.1, R134.2
unnamed: LED20.1, R135.2
unnamed: Q19.B, R136.2
unnamed: Q20.B, R137.2
unnamed: R128.2, U30.5
unnamed: R127.2, U30.4
unnamed: R138.2, U30.9
unnamed: R139.2, R140.2, U30.8
RTS: Q2.E, R14.1, U2.24
RTS1: Q3.E, R25.1, U6.24
RTS2: Q5.E, R39.1, U9.24
RTS3: Q7.E, R53.1, U12.24
RTS4: Q9.E, R67.1, U15.24
RTS5: Q11.E, R81.1, U18.24
RTS6: Q13.E, R95.1, U21.24
RTS7: Q15.E, R109.1, U24.24
RTS8: Q17.E, R123.1, U27.24
RTS9: Q19.E, R137.1, U30.24
RXD: J2.P5, J6.P5, U1.36, U2.26
RXD1: J8.P5, J12.P5, U5.36, U6.26
RXD2: J14.P5, J18.P5, U8.36, U9.26
RXD3: J20.P5, J24.P5, U11.36, U12.26
RXD4: J26.P5, J30.P5, U14.36, U15.26
RXD5: J32.P5, J36.P5, U17.36, U18.26
RXD6: J38.P5, J42.P5, U20.36, U21.26
RXD7: J44.P5, J48.P5, U23.36, U24.26
RXD8: J50.P5, J54.P5, U26.36, U27.26
RXD9: J56.P5, J60.P5, U29.36, U30.26
TXD: J2.P4, J6.P4, U1.37, U2.25
TXD1: J8.P4, J12.P4, U5.37, U6.25
TXD2: J14.P4, J18.P4, U8.37, U9.25
TXD3: J20.P4, J24.P4, U11.37, U12.25
TXD4: J26.P4, J30.P4, U14.37, U15.25
TXD5: J32.P4, J36.P4, U17.37, U18.25
TXD6: J38.P4, J42.P4, U20.37, U21.25
TXD7: J44.P4, J48.P4, U23.37, U24.25
TXD8: J50.P4, J54.P4, U26.37, U27.25
TXD9: J56.P4, J60.P4, U29.37, U30.25
V_USB: C3.2, C6.2, D1.2, JB2.P$1, R11.1, USB1.A4B9, USB1.B4A9
V_USB1: C16.2, C17.2, D2.2, JB4.P$1, R27.1, USB2.A4B9, USB2.B4A9
V_USB2: C29.2, C30.2, D3.2, JB6.P$1, R41.1, USB3.A4B9, USB3.B4A9
V_USB3: C42.2, C43.2, D4.2, JB8.P$1, R55.1, USB4.A4B9, USB4.B4A9
V_USB4: C55.2, C56.2, D5.2, JB10.P$1, R69.1, USB5.A4B9, USB5.B4A9
V_USB5: C68.2, C69.2, D6.2, JB12.P$1, R83.1, USB6.A4B9, USB6.B4A9
V_USB6: C81.2, C82.2, D7.2, JB14.P$1, R97.1, USB7.A4B9, USB7.B4A9
V_USB7: C94.2, C95.2, D8.2, JB16.P$1, R111.1, USB8.A4B9, USB8.B4A9
V_USB8: C107.2, C108.2, D9.2, JB18.P$1, R125.1, USB9.A4B9, USB9.B4A9
V_USB9: C120.2, C121.2, D10.2, JB20.P$1, R139.1, USB10.A4B9, USB10.B4A9
